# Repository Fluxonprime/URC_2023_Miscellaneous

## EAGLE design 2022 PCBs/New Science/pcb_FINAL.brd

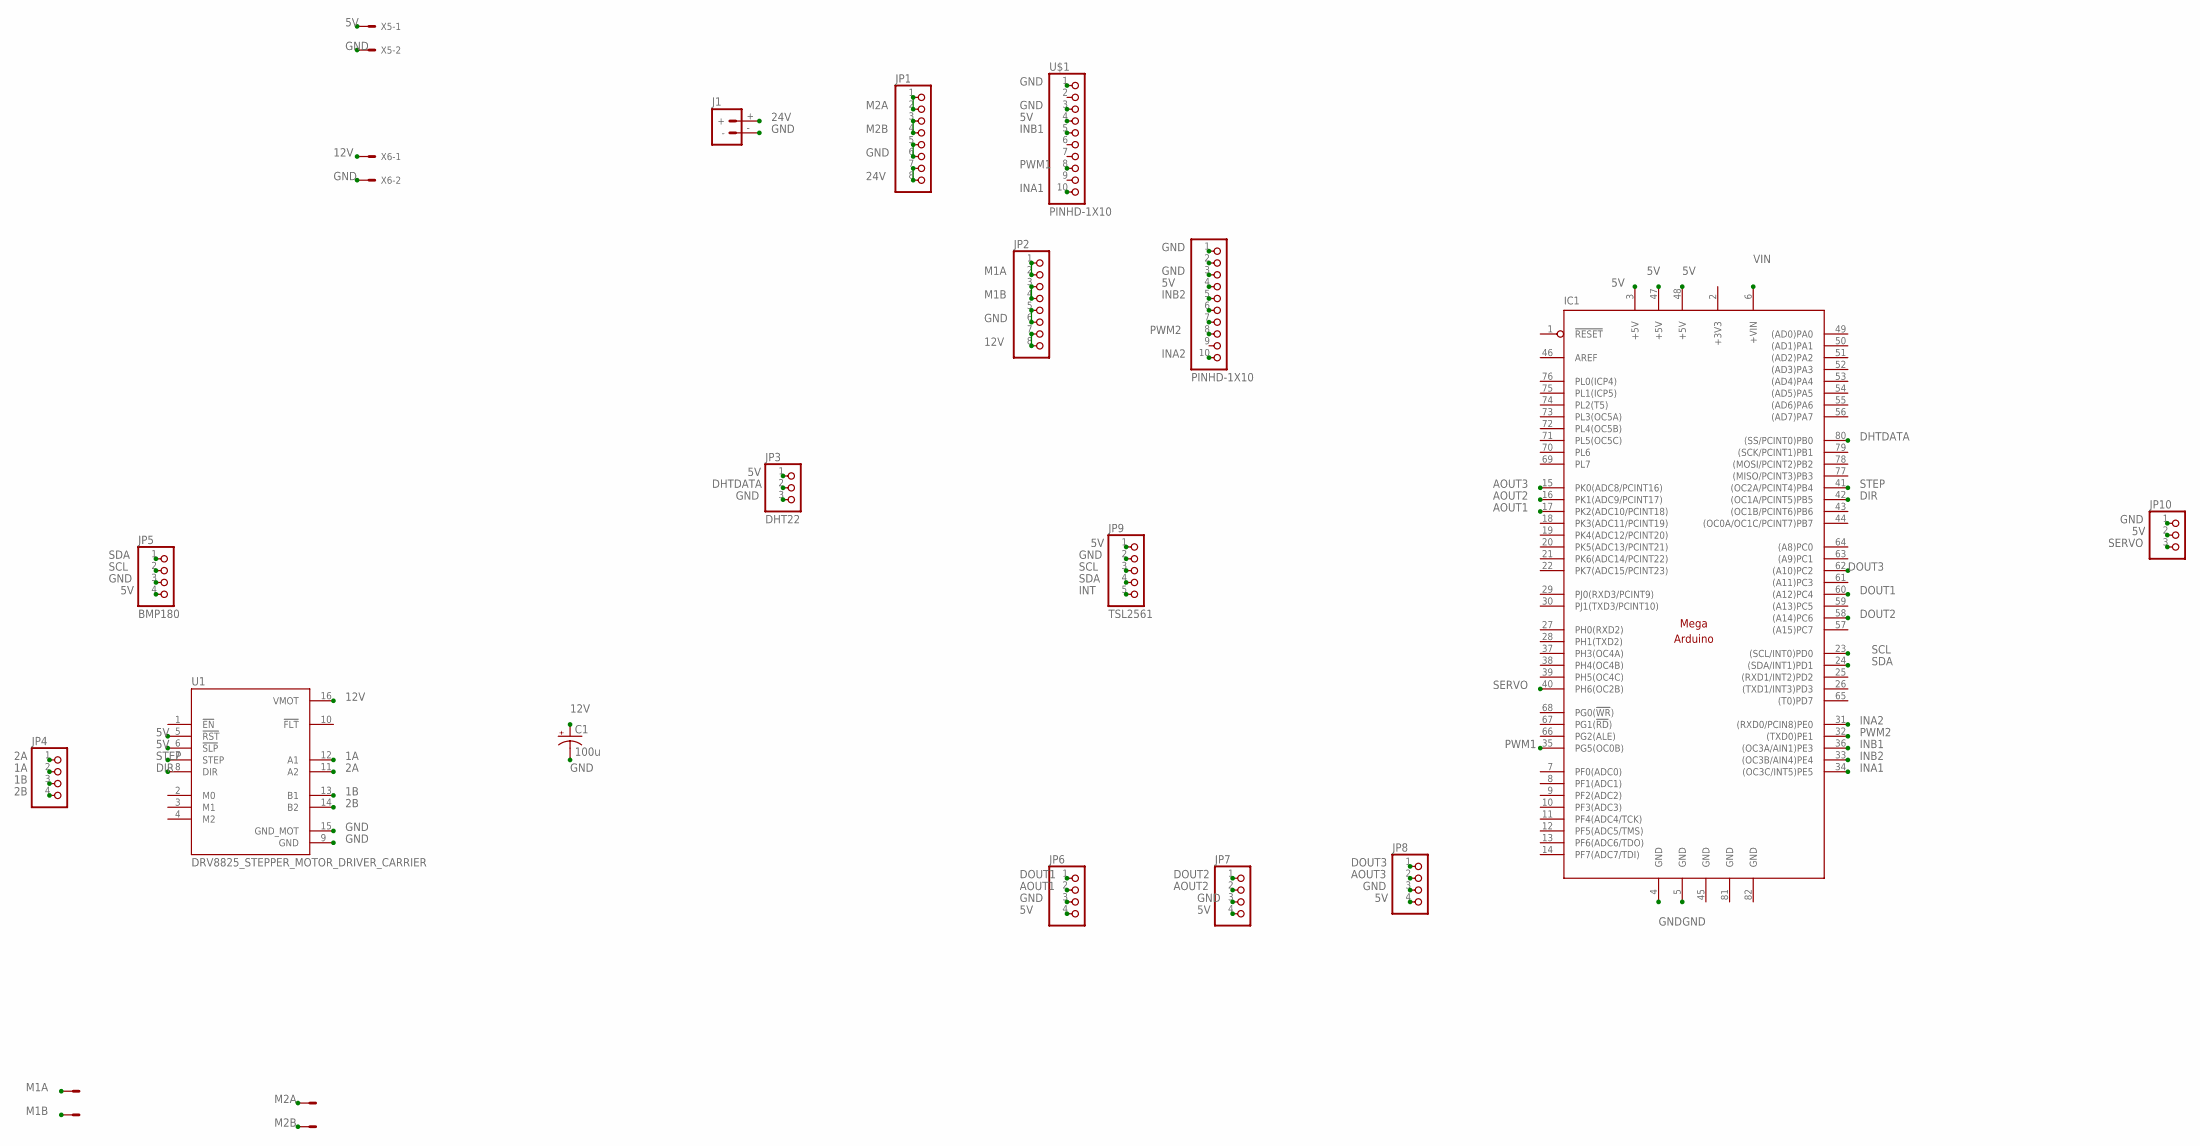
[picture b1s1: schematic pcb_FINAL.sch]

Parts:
C1: 100u; R/2012-12W
IC1: ARDUINO_MEGAARDUINO_11; ARDUINO_MEGA_ARDUINO_1
J1: BATTERY_CONN_DEANS; DEANS
JP1, JP2: PINHD-1X8BIG; 1X08-BIG
JP3: DHT22; 1X03
JP4, JP6, JP7, JP8: PINHD-1X4; 1X04
JP5: BMP180; 1X04
JP9: TSL2561; 1X05
JP10: PINHD-1X3; 1X03
U1: DRV8825_STEPPER_MOTOR_DRIVER_CARRIER; IC_DRV8825_STEPPER_MOTOR_DRIVER_CARRIER
U$1, U$2: PINHD-1X10; 1X10-BIG
X3, X4, X5, X6: KK-156-2

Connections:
1A: JP4.2, U1.12 (A1)
1B: JP4.3, U1.13 (B1)
2A: JP4.1, U1.11 (A2)
2B: JP4.4, U1.14 (B2)
5V: IC1.3 (+5V), IC1.47 (+5V), IC1.48 (+5V), JP3.1, JP5.4, JP6.4, JP7.4, JP8.4, JP9.1, JP10.2, U1.5 (!RST), U1.6 (!SLP), U$1.4, U$2.4, X5.1
12V: C1.+, JP2.7, JP2.8, U1.16 (VMOT), X6.1
24V: J1.+, JP1.7, JP1.8
+3V3: IC1.2 (+3V3)
AOUT1: IC1.17 (PK2(ADC10/PCINT18)), JP6.2
AOUT2: IC1.16 (PK1(ADC9/PCINT17)), JP7.2
AOUT3: IC1.15 (PK0(ADC8/PCINT16)), JP8.2
DHTDATA: IC1.80 ((SS/PCINT0)PB0), JP3.2
DIR: IC1.42 ((OC1A/PCINT5)PB5), U1.8 (DIR)
DOUT1: IC1.60 ((A12)PC4), JP6.1
DOUT2: IC1.58 ((A14)PC6), JP7.1
DOUT3: IC1.62 ((A10)PC2), JP8.1
GND: C1.-, IC1.4 (GND), IC1.5 (GND), IC1.45 (GND), IC1.81 (GND), IC1.82 (GND), J1.-, JP1.5, JP1.6, JP2.5, JP2.6, JP3.3, JP5.3, JP6.3, JP7.3, JP8.3, JP9.2, JP10.1, U1.9 (GND), U1.15 (GND_MOT), U$1.1, U$1.3, U$2.1, U$2.3, X5.2, X6.2
INA1: IC1.34 ((OC3C/INT5)PE5), U$1.10
INA2: IC1.31 ((RXD0/PCIN8)PE0), U$2.10
INB1: IC1.36 ((OC3A/AIN1)PE3), U$1.5
INB2: IC1.33 ((OC3B/AIN4)PE4), U$2.5
INT: JP9.5
M1A: JP2.1, JP2.2, X3.1
M1B: JP2.3, JP2.4, X3.2
M2A: JP1.1, JP1.2, X4.1
M2B: JP1.3, JP1.4, X4.2
PWM1: IC1.35 (PG5(OC0B)), U$1.8
PWM2: IC1.32 ((TXD0)PE1), U$2.8
SCL: IC1.23 ((SCL/INT0)PD0), JP5.2, JP9.3
SDA: IC1.24 ((SDA/INT1)PD1), JP5.1, JP9.4
SERVO: IC1.40 (PH6(OC2B)), JP10.3
STEP: IC1.41 ((OC2A/PCINT4)PB4), U1.7 (STEP)
VIN: IC1.6 (+VIN)

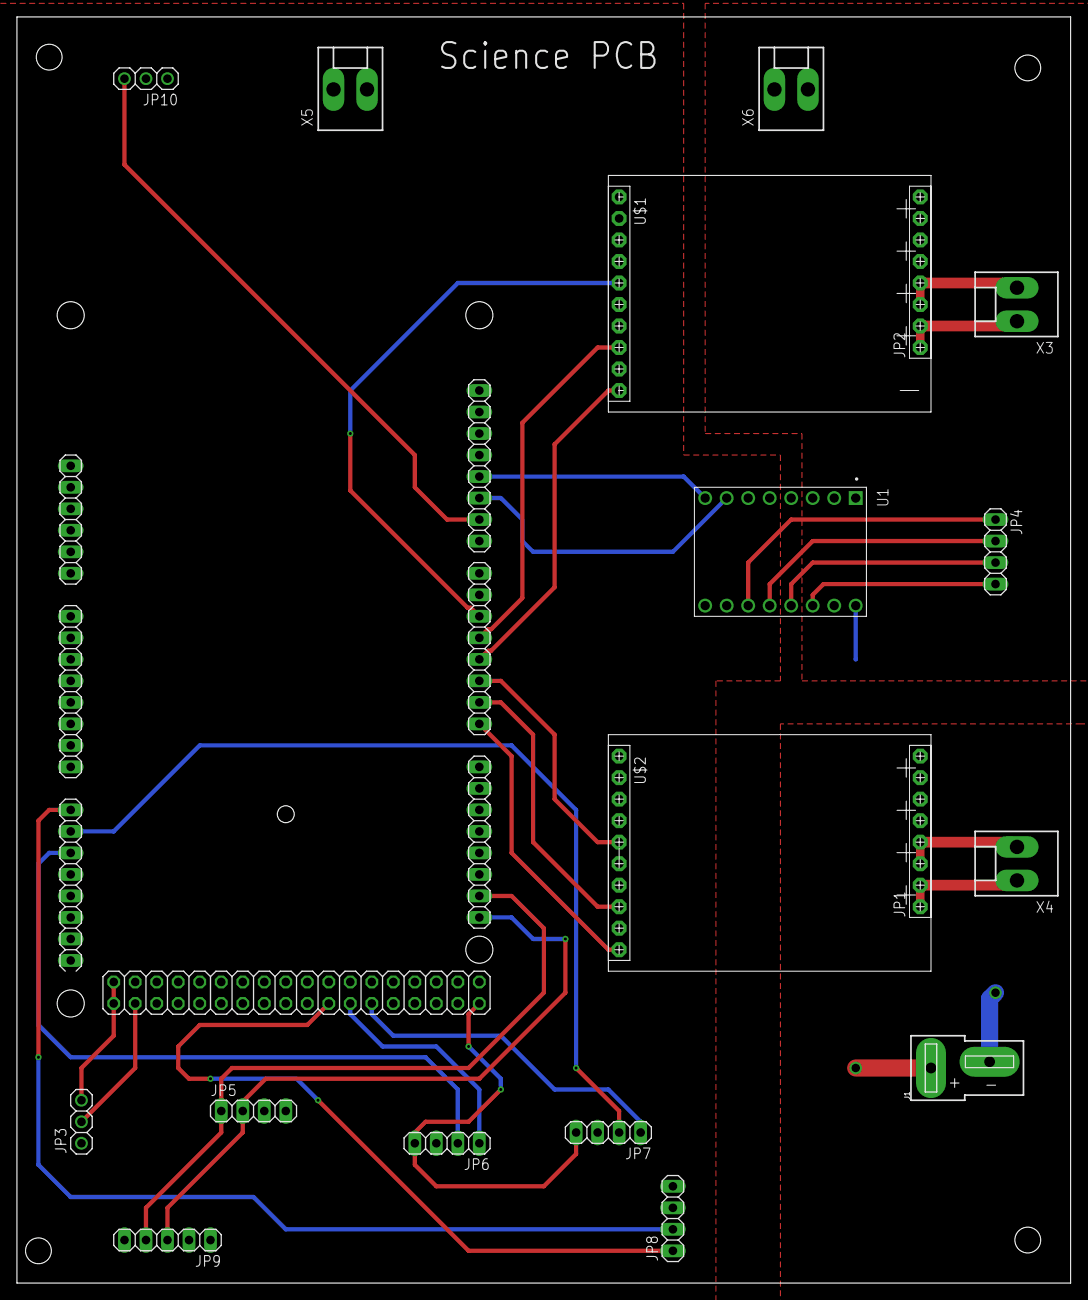
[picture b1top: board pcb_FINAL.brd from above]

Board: 2 copper layers, 124.4 x 149.5 mm, 20 parts (1 on the bottom side), 30 nets.

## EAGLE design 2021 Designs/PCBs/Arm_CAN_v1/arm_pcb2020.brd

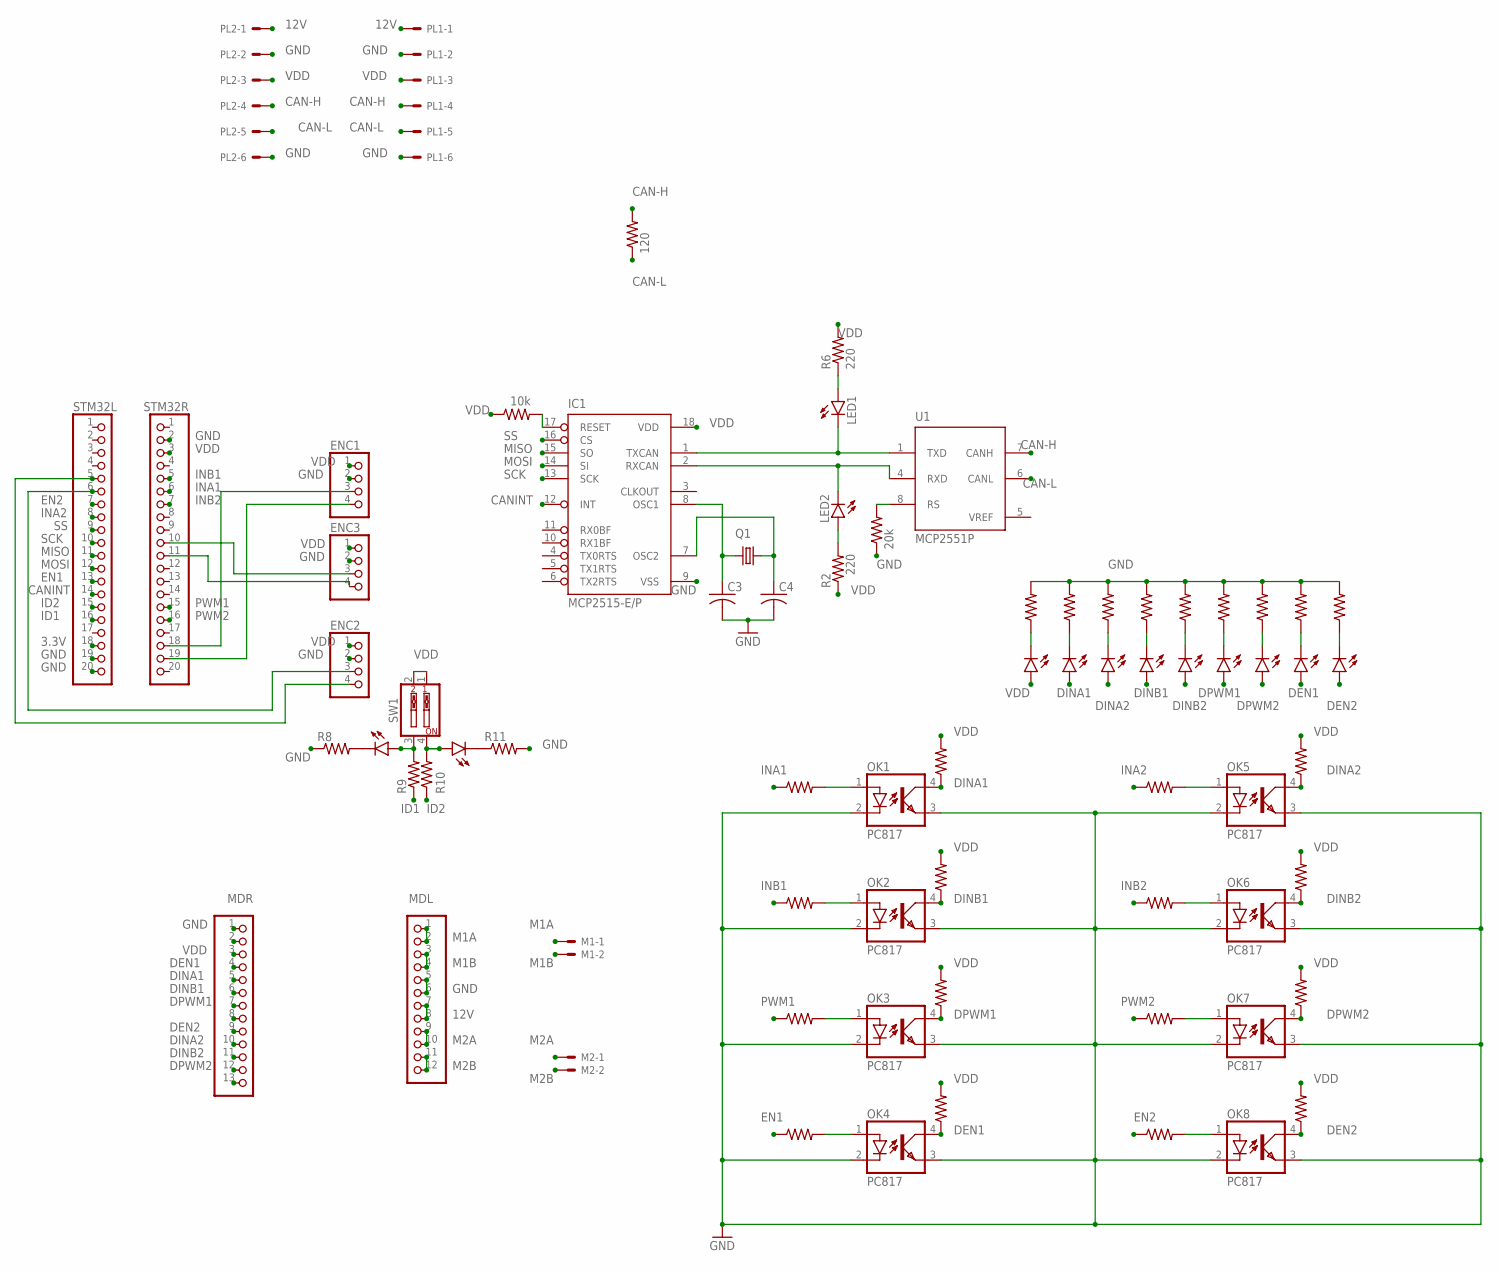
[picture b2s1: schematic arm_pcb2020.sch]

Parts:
C3, C4: C-US025-024X044; C025-024X044
ENC1, ENC2, ENC3: PINHD-1X4; 1X04
IC1: MCP2515-E/P; DIL18
JP2: MDL; 1X12
LED1, LED2, LED7, LED8, LED10, LED11, LED12, LED13, LED14, LED15, LED16, LED17, LED18: LEDSMT1206; 1206
M1, M2: 22-23-2021
MDR: MDR; 1X13
OK1, OK2, OK3, OK4, OK5, OK6, OK7, OK8: PC817; DIL04
PL1, PL2: 555X-6V; 5566-6
Q1: CRYSTALHC49U-V; HC49U-V
R2, R6: 220; R0805
R3: 120; 0207/9
R4, R5, R7, R8, R9, R10, R11, R12, R13, R14, R15, R16, R17, R18, R19, R20, R21, R22, R23, R24, R25, R26, R27, R28, R29, R33, R34, R37, R38: R-US_R0805; R0805
R39: 10k; 0207/10
R40: 20k; 0207/10
STM32L, STM32R: PINHD-1X20; 1X20
SW1: SW_DIP-2; EDG-02
U1: MCP2551P; DIL8

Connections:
3.3V: STM32L.18
12V: JP2.7, JP2.8, PL1.1, PL2.1
CAN-H: PL1.4, PL2.4, R3.2, U1.7 (CANH)
CAN-L: PL1.5, PL2.5, R3.1, U1.6 (CANL)
CANINT: IC1.12 (INT), STM32L.14
DEN1: LED17.A, MDR.4, OK4.4 (COL), R13.1
DEN2: LED18.A, MDR.9, OK8.4 (COL), R26.1
DINA1: LED11.A, MDR.5, OK1.4 (COL), R4.1
DINA2: LED12.A, MDR.10, OK5.4 (COL), R29.1
DINB1: LED13.A, MDR.6, OK2.4 (COL), R5.1
DINB2: LED14.A, MDR.11, OK6.4 (COL), R28.1
DPWM1: LED15.A, MDR.7, OK3.4 (COL), R12.1
DPWM2: LED16.A, MDR.12, OK7.4 (COL), R27.1
EN1: R23.1, STM32L.13
EN2: R38.1, STM32L.7
GND: C3.2, C4.2, ENC1.2, ENC2.2, ENC3.2, IC1.9 (VSS), JP2.5, JP2.6, MDR.1, OK1.2 (C), OK1.3 (EMIT), OK2.2 (C), OK2.3 (EMIT), OK3.2 (C), OK3.3 (EMIT), OK4.2 (C), OK4.3 (EMIT), OK5.2 (C), OK5.3 (EMIT), OK6.2 (C), OK6.3 (EMIT), OK7.2 (C), OK7.3 (EMIT), OK8.2 (C), OK8.3 (EMIT), PL1.2, PL1.6, PL2.2, PL2.6, R8.1, R11.2, R14.2, R15.2, R16.2, R17.2, R18.2, R19.2, R20.2, R33.2, R34.2, R40.1, STM32L.19, STM32L.20, STM32R.2
ID1: R9.1, STM32L.16
ID2: R10.1, STM32L.15
INA1: R7.1, STM32R.6
INA2: R24.1, STM32L.8
INB1: R21.1, STM32R.5
INB2: R25.1, STM32R.7
M1A: JP2.1, JP2.2, M1.1
M1B: JP2.3, JP2.4, M1.2
M2A: JP2.9, JP2.10, M2.1
M2B: JP2.11, JP2.12, M2.2
MISO: IC1.15 (SO), STM32L.11
MOSI: IC1.14 (SI), STM32L.12
unnamed: IC1.1 (TXCAN), LED1.C, U1.1 (TXD)
unnamed: R40.2, U1.8 (RS)
unnamed: C4.1, IC1.7 (OSC2), Q1.2
unnamed: C3.1, IC1.8 (OSC1), Q1.1
unnamed: LED11.C, R15.1
unnamed: ENC1.4, STM32R.19
unnamed: OK1.1 (A), R7.2
unnamed: LED12.C, R16.1
unnamed: IC1.17 (RESET), R39.2
unnamed: LED7.A, R9.2, SW1.3
unnamed: LED8.A, R10.2, SW1.4
unnamed: LED8.C, R11.1
unnamed: LED7.C, R8.2
unnamed: LED13.C, R17.1
unnamed: ENC2.4, STM32L.5
unnamed: OK2.1 (A), R21.2
unnamed: LED10.C, R14.1
unnamed: LED14.C, R18.1
unnamed: LED15.C, R19.1
unnamed: LED16.C, R20.1
unnamed: LED17.C, R33.1
unnamed: ENC2.3, STM32L.6
unnamed: ENC1.3, STM32R.18
unnamed: LED18.C, R34.1
unnamed: ENC3.3, STM32R.10
unnamed: LED2.A, R2.2
unnamed: ENC3.4, STM32R.11
unnamed: LED1.A, R6.1
unnamed: IC1.2 (RXCAN), LED2.C, U1.4 (RXD)
unnamed: OK3.1 (A), R22.2
unnamed: OK4.1 (A), R23.2
unnamed: OK5.1 (A), R24.2
unnamed: OK6.1 (A), R25.2
unnamed: OK7.1 (A), R37.2
unnamed: OK8.1 (A), R38.2
PWM1: R22.1, STM32R.15
PWM2: R37.1, STM32R.16
SCK: IC1.13 (SCK), STM32L.10
SS: IC1.16 (CS), STM32L.9
VDD: ENC1.1, ENC2.1, ENC3.1, IC1.18 (VDD), LED10.A, MDR.3, PL1.3, PL2.3, R2.1, R4.2, R5.2, R6.2, R12.2, R13.2, R26.2, R27.2, R28.2, R29.2, R39.1, STM32R.3, SW1.1, SW1.2, U1.3 (VDD)
VREF: U1.5 (VREF)
VSS: U1.2 (VSS)

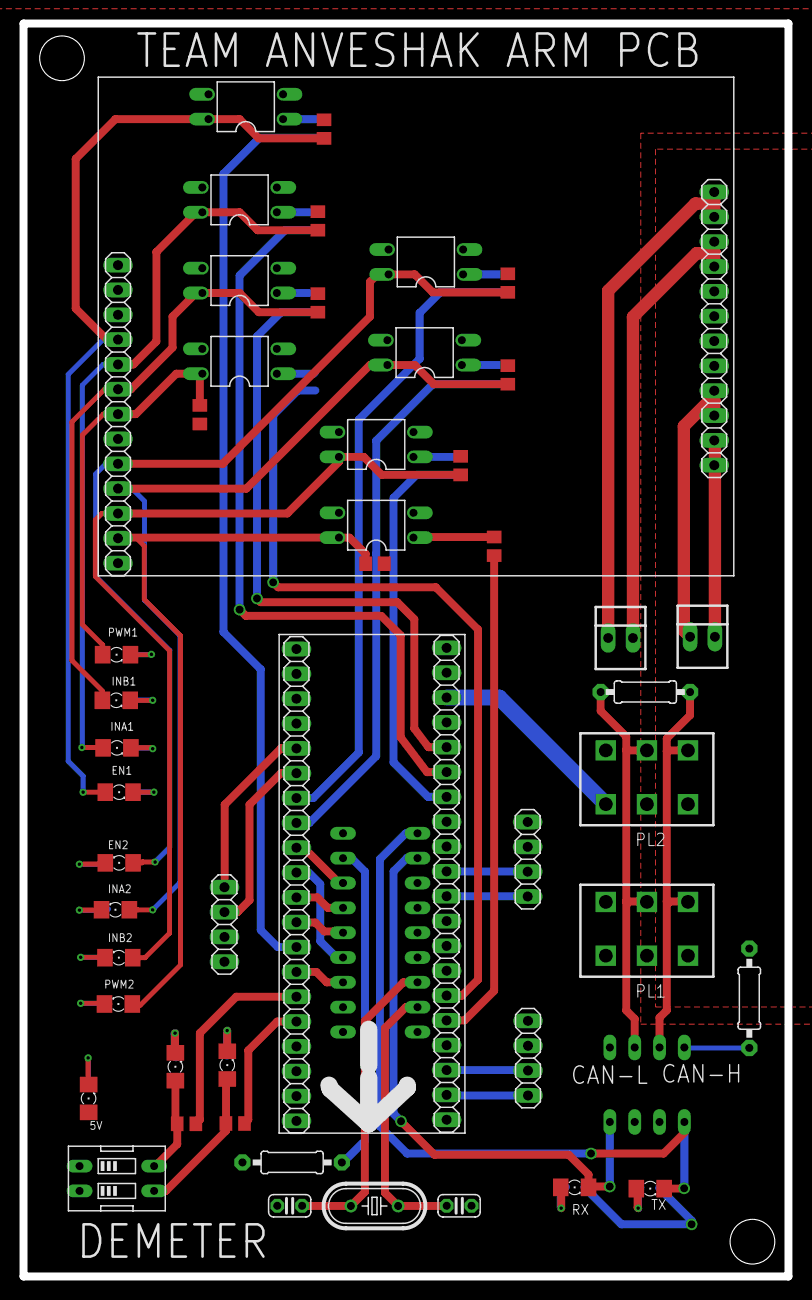
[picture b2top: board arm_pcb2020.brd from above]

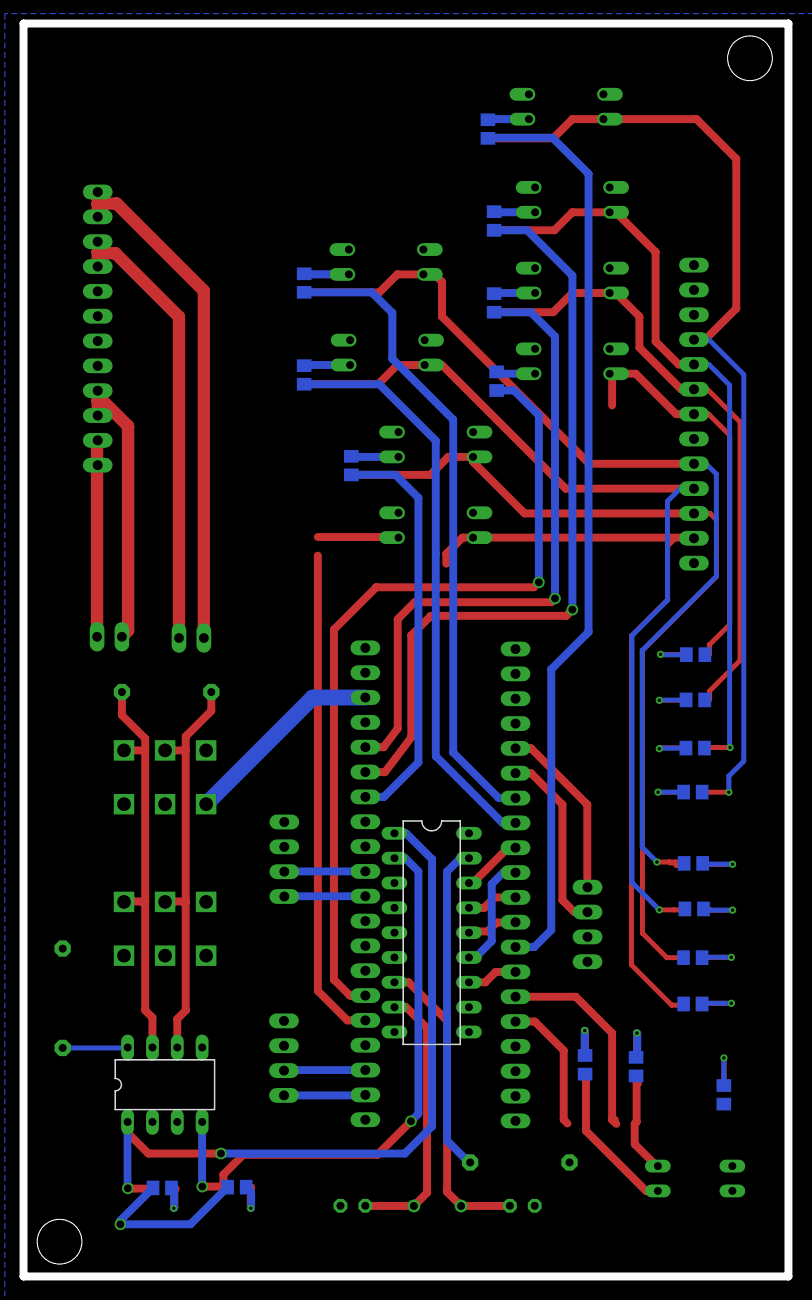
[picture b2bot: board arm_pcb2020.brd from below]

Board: 2 copper layers, 78.2 x 128.1 mm, 72 parts (22 on the bottom side), 67 nets.

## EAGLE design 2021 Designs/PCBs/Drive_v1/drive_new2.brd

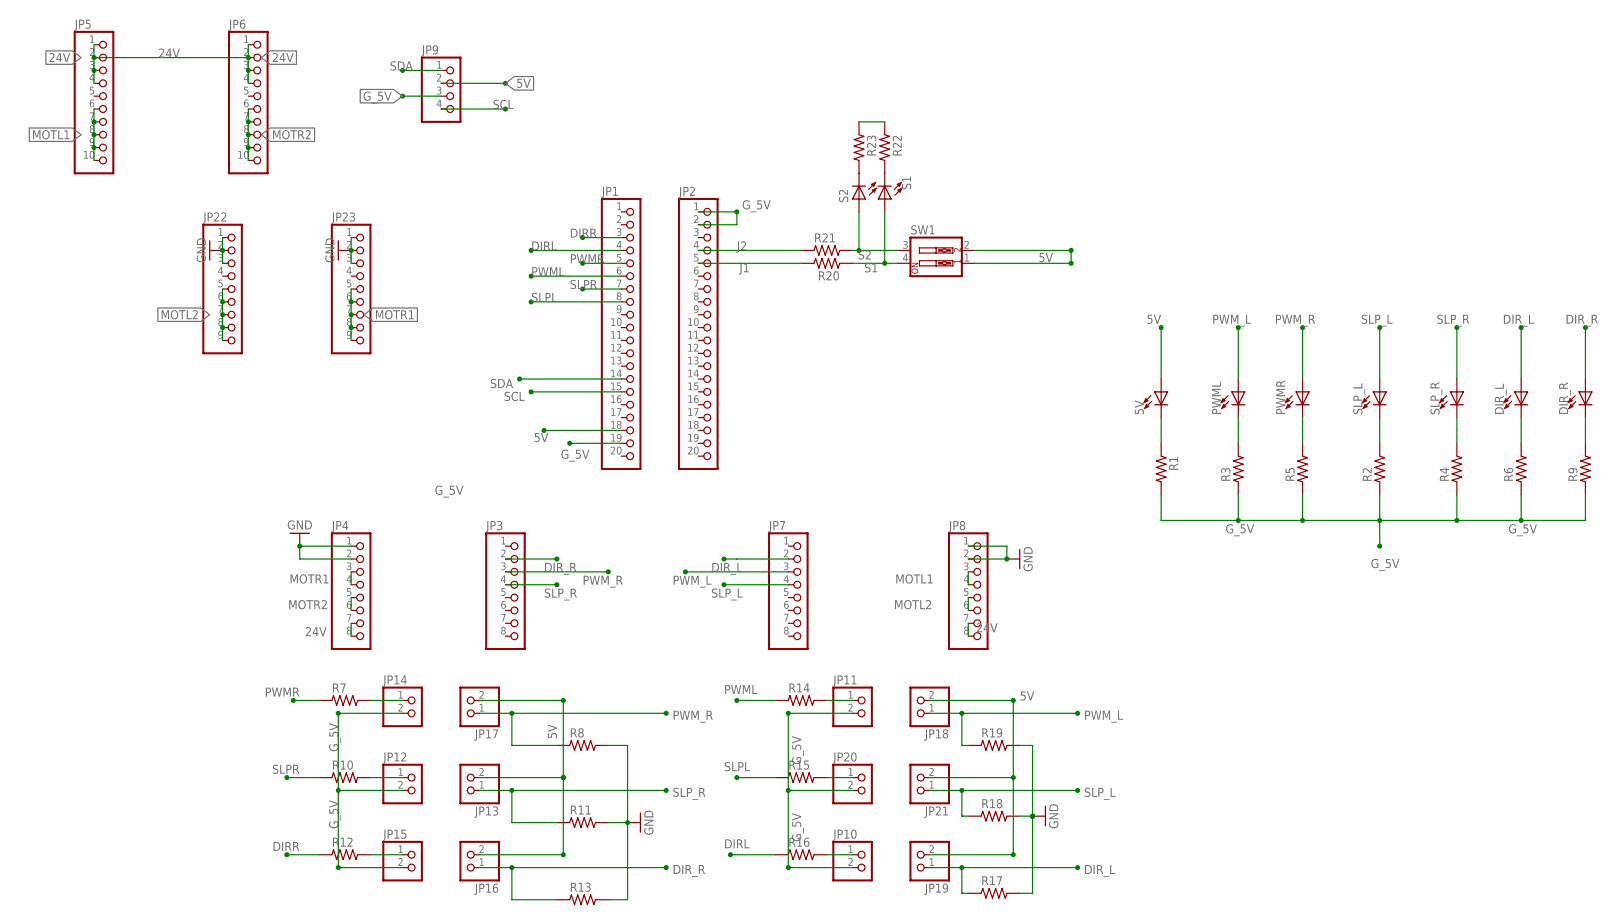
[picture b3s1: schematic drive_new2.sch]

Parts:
5V: RED; LED_1206
DIR_L: BLUE; LED_1206
DIR_R: BLUE; LED_1206
JP1, JP2: PINHD-1X20; 1X20
JP3, JP4, JP7, JP8: PINHD-1X8; 1X08
JP5, JP6: PINHD-1X10; 1X10
JP9: PINHD-1X4; 1X04
JP10, JP11, JP12, JP13, JP14, JP15, JP16, JP17, JP18, JP19, JP20, JP21: PINHD-1X2; 1X02
JP22, JP23: PINHD-1X9; 1X09
PWML: RED; LED_1206
PWMR: RED; LED_1206
R1, R2, R3, R4, R5, R6, R7, R8, R9, R10, R11, R12, R13, R14, R15, R16, R17, R18, R19, R20, R21, R22, R23: R_0805; R0805
S1, S2: RED; LED_1206
SLP_L: BLUE; LED_1206
SLP_R: BLUE; LED_1206
SW1: SW_DIP-2; EDG-02

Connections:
5V: 5V.A, JP1.18, JP9.2, JP13.2, JP16.2, JP17.2, JP18.2, JP19.2, JP21.2, SW1.1, SW1.2
24V: JP4.7, JP4.8, JP5.1, JP5.2, JP5.3, JP5.4, JP6.1, JP6.2, JP6.3, JP6.4, JP8.7, JP8.8
DIRL: JP1.4, R16.1
DIRR: JP1.3, R12.1
DIR_L: DIR_L.A, JP7.2, JP19.1, R17.1
DIR_R: DIR_R.A, JP3.2, JP16.1, R13.1
GND: JP4.1, JP4.2, JP8.1, JP8.2, JP22.1, JP22.2, JP22.3, JP23.1, JP23.2, JP23.3, R8.2, R11.2, R13.2, R17.2, R18.2, R19.2
G_5V: JP1.19, JP2.1, JP2.2, JP9.3, JP10.2, JP11.2, JP12.2, JP14.2, JP15.2, JP20.2, R1.2, R2.1, R3.1, R4.1, R5.1, R6.1, R9.1, R22.1, R23.1
J1: JP2.5, R20.2
J2: JP2.4, R21.2
MOTL1: JP5.6, JP5.7, JP5.8, JP5.9, JP5.10, JP8.3, JP8.4
MOTL2: JP8.5, JP8.6, JP22.5, JP22.6, JP22.7, JP22.8, JP22.9
MOTR1: JP4.3, JP4.4, JP23.5, JP23.6, JP23.7, JP23.8, JP23.9
MOTR2: JP4.5, JP4.6, JP6.6, JP6.7, JP6.8, JP6.9, JP6.10
unnamed: DIR_R.C, R9.2
unnamed: DIR_L.C, R6.2
unnamed: R4.2, SLP_R.C
unnamed: R2.2, SLP_L.C
unnamed: PWMR.C, R5.2
unnamed: PWML.C, R3.2
unnamed: 5V.C, R1.1
unnamed: JP14.1, R7.2
unnamed: JP12.1, R10.2
unnamed: R22.2, S1.C
unnamed: JP15.1, R12.2
unnamed: R23.2, S2.C
unnamed: JP11.1, R14.2
unnamed: JP20.1, R15.2
unnamed: JP10.1, R16.2
PWML: JP1.6, R14.1
PWMR: JP1.5, R7.1
PWM_L: JP7.3, JP18.1, PWML.A, R19.1
PWM_R: JP3.3, JP17.1, PWMR.A, R8.1
S1: R20.1, S1.A, SW1.4
S2: R21.1, S2.A, SW1.3
SCL: JP1.15, JP9.4
SDA: JP1.14, JP9.1
SLPL: JP1.8, R15.1
SLPR: JP1.7, R10.1
SLP_L: JP7.4, JP21.1, R18.1, SLP_L.A
SLP_R: JP3.4, JP13.1, R11.1, SLP_R.A

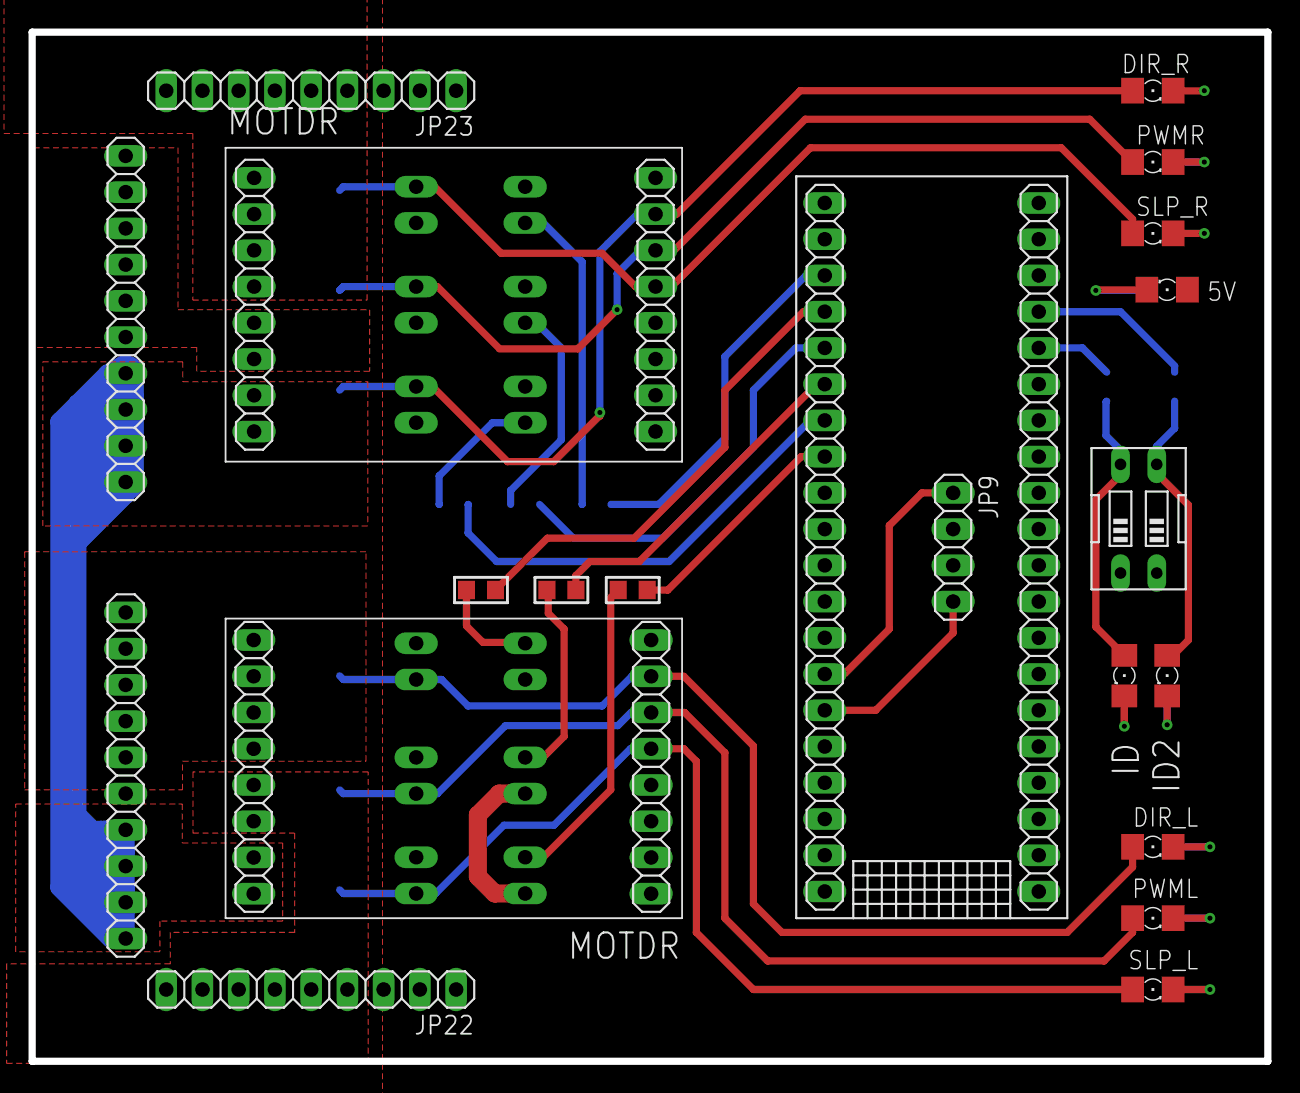
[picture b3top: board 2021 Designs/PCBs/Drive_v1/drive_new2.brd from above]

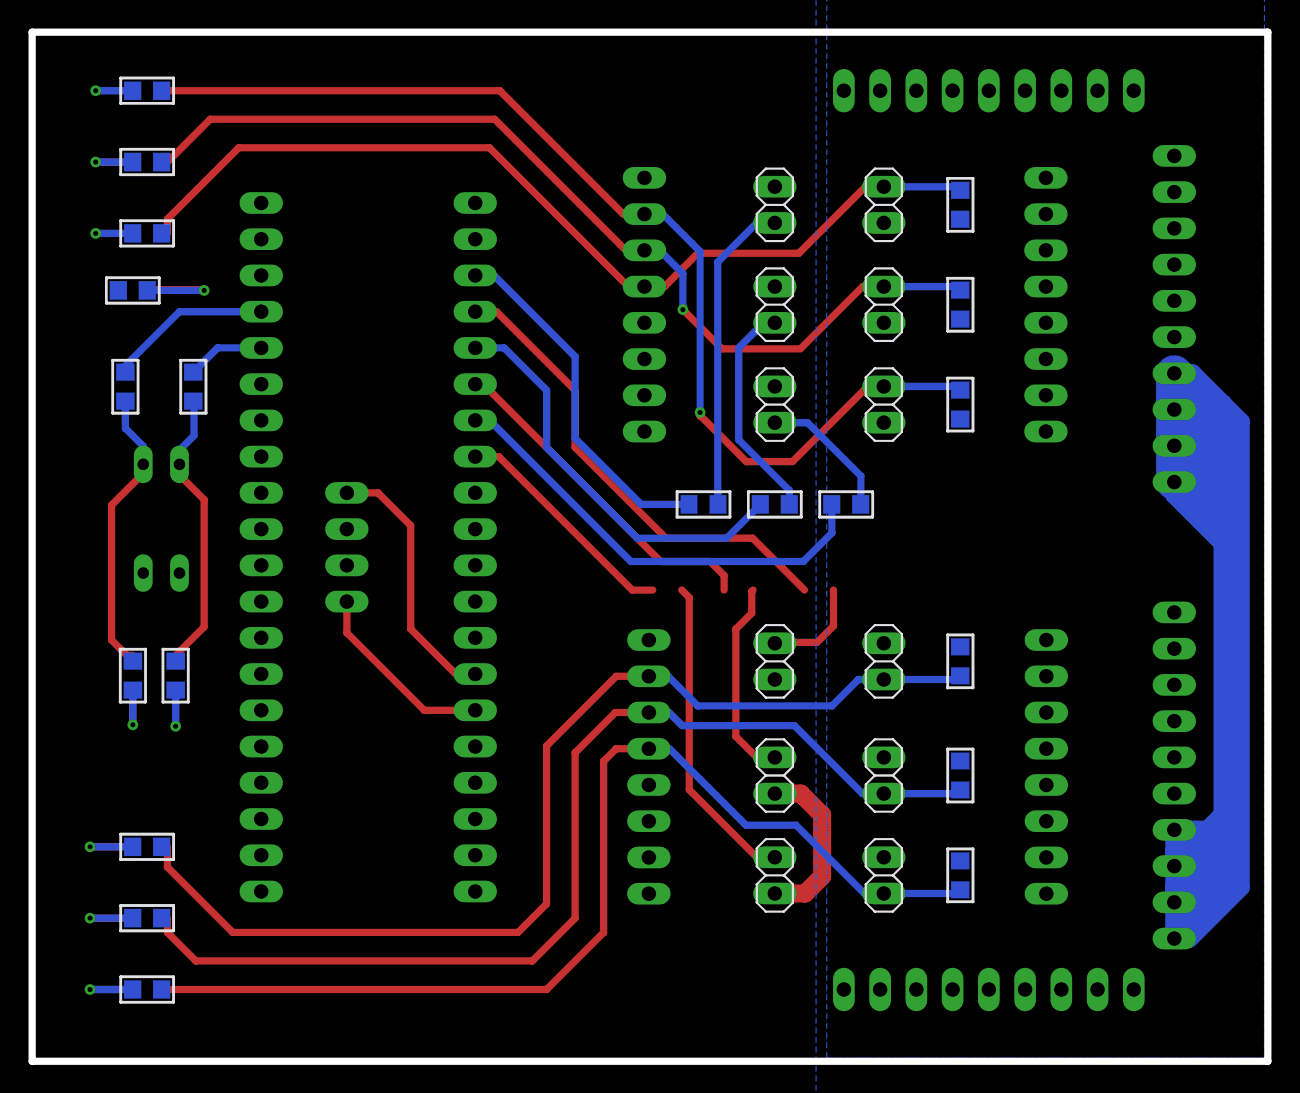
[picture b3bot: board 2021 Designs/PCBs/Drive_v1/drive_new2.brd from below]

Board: 2 copper layers, 86.6 x 72.1 mm, 56 parts (32 on the bottom side), 41 nets.

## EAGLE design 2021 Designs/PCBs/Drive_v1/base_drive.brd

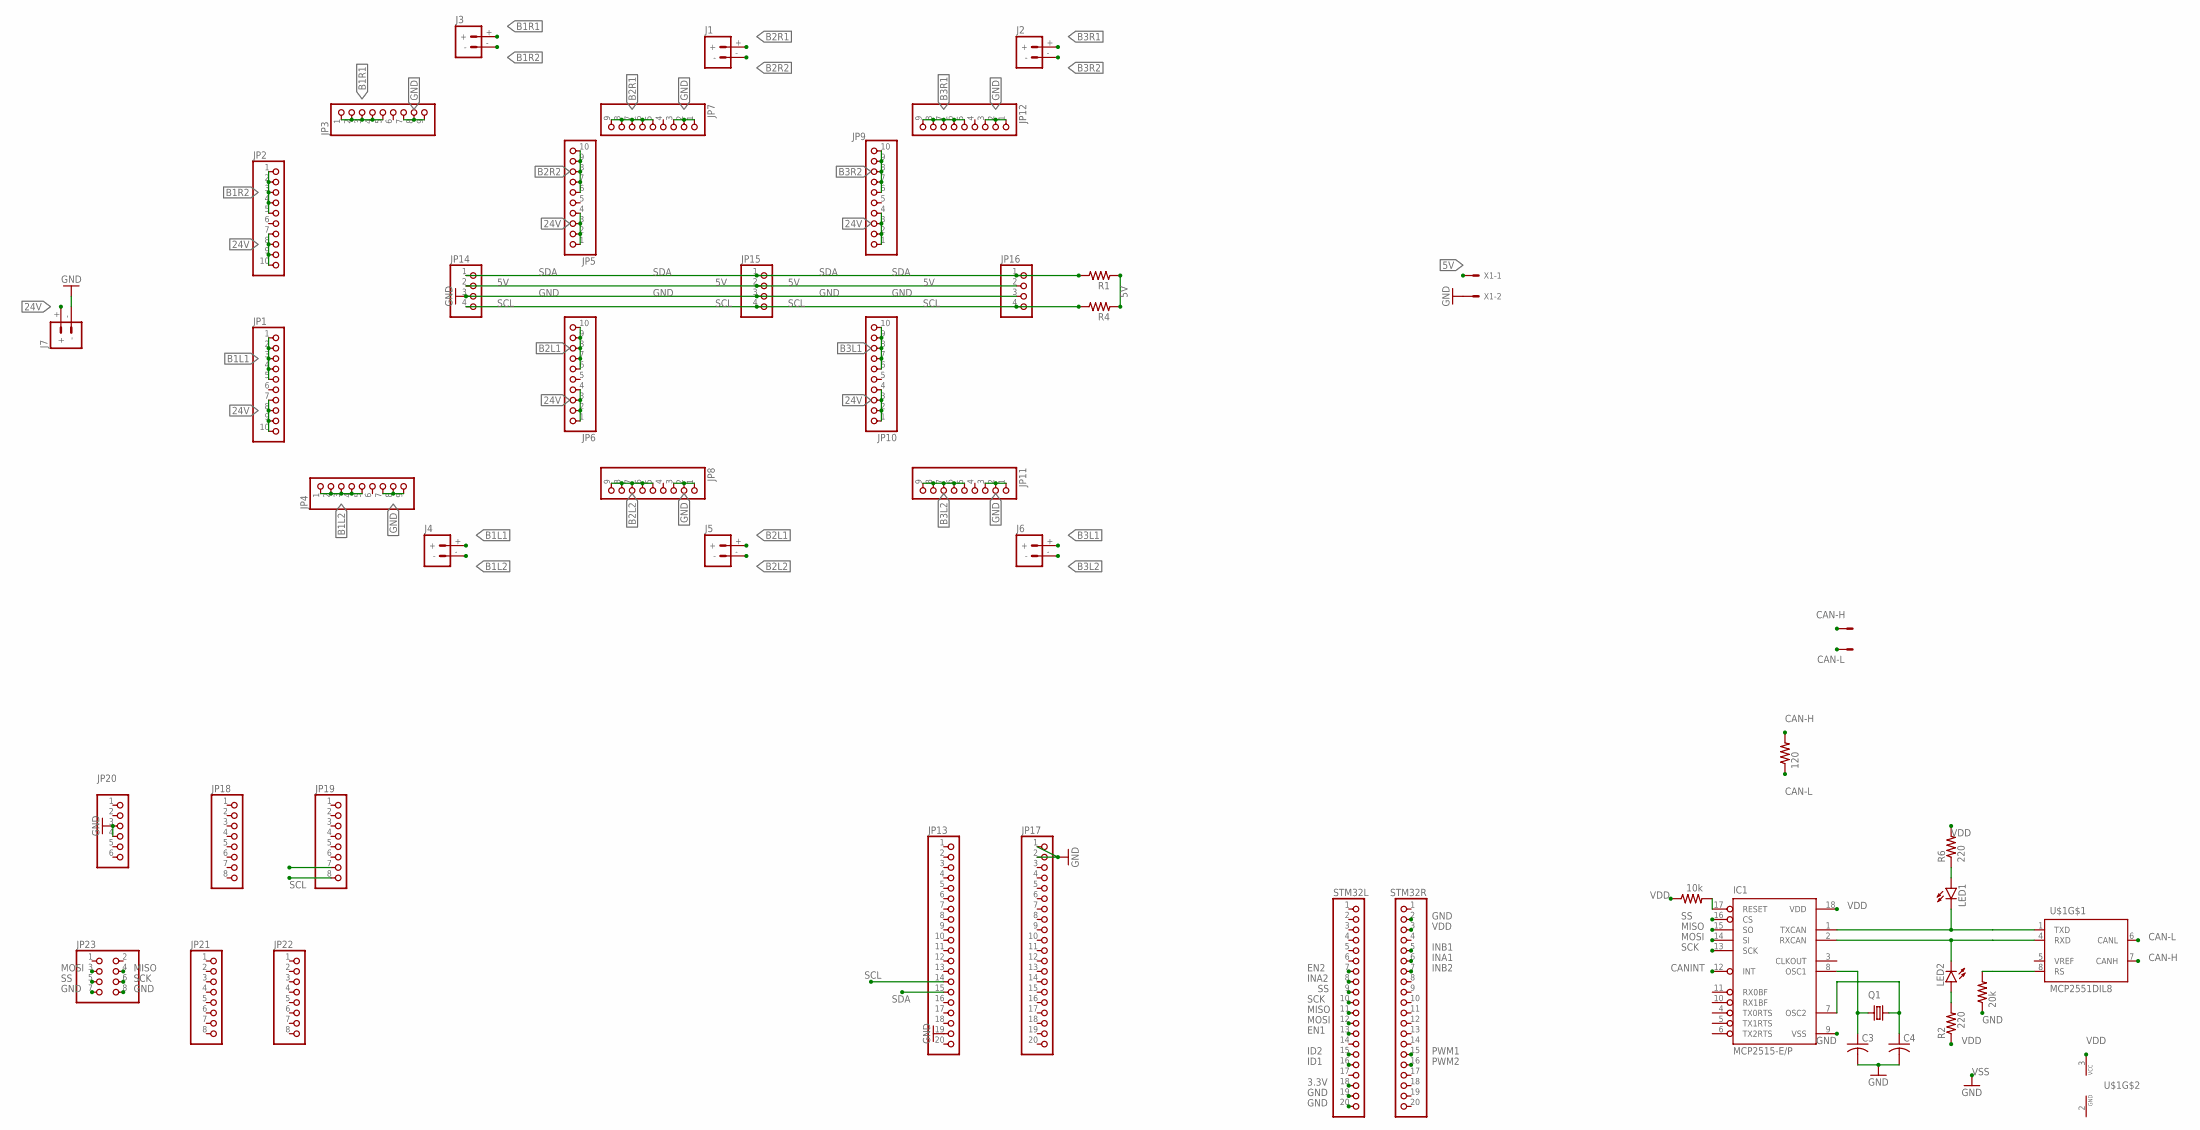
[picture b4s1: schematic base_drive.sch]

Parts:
C3, C4: C-US025-024X044; C025-024X044
IC1: MCP2515-E/P; DIL18
J1, J2, J3, J4, J5, J6, J7: BATTERY_CONN_DEANS; DEANS
JP1, JP2, JP5, JP6, JP9, JP10: PINHD-1X10; 1X10
JP3, JP4, JP7, JP8, JP11, JP12: PINHD-1X9; 1X09
JP13, JP17: PINHD-1X20; 1X20
JP14, JP15, JP16: PINHD-1X4; 1X04
JP18, JP19, JP21, JP22: PINHD-1X8; 1X08
JP20: PINHD-1X6; 1X06
JP23: PINHD-2X4; 2X04
LED1, LED2: LEDSMT1206; 1206
Q1: CRYSTALHC49U-V; HC49U-V
R1, R4: R_1206; R1206
R2, R6: 220; R0805
R3: 120; 0207/9
R39: 10k; 0207/10
R40: 20k; 0207/10
STM32L, STM32R: PINHD-1X20; 1X20
U$1: MCP2551DIL8; DIL08
X1, X2: KK-156-2

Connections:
3.3V: STM32L.18
5V: JP14.2, JP15.2, JP16.2, R1.1, R4.1, X1.1
24V: J7.+, JP1.7, JP1.8, JP1.9, JP1.10, JP2.7, JP2.8, JP2.9, JP2.10, JP5.1, JP5.2, JP5.3, JP5.4, JP6.1, JP6.2, JP6.3, JP6.4, JP9.1, JP9.2, JP9.3, JP9.4, JP10.1, JP10.2, JP10.3, JP10.4
B1L1: J4.+, JP1.1, JP1.2, JP1.3, JP1.4, JP1.5
B1L2: J4.-, JP4.1, JP4.2, JP4.3, JP4.4, JP4.5
B1R1: J3.+, JP3.1, JP3.2, JP3.3, JP3.4, JP3.5
B1R2: J3.-, JP2.1, JP2.2, JP2.3, JP2.4, JP2.5
B2L1: J5.+, JP6.6, JP6.7, JP6.8, JP6.9, JP6.10
B2L2: J5.-, JP8.5, JP8.6, JP8.7, JP8.8, JP8.9
B2R1: J1.+, JP7.5, JP7.6, JP7.7, JP7.8, JP7.9
B2R2: J1.-, JP5.6, JP5.7, JP5.8, JP5.9, JP5.10
B3L1: J6.+, JP10.6, JP10.7, JP10.8, JP10.9, JP10.10
B3L2: J6.-, JP11.5, JP11.6, JP11.7, JP11.8, JP11.9
B3R1: J2.+, JP12.5, JP12.6, JP12.7, JP12.8, JP12.9
B3R2: J2.-, JP9.6, JP9.7, JP9.8, JP9.9, JP9.10
CAN-H: R3.2, U$1.7 (CANH), X2.1
CAN-L: R3.1, U$1.6 (CANL), X2.2
CANINT: IC1.12 (INT)
EN1: STM32L.13
EN2: STM32L.7
GND: C3.2, C4.2, IC1.9 (VSS), J7.-, JP3.7, JP3.8, JP3.9, JP4.7, JP4.8, JP4.9, JP7.1, JP7.2, JP7.3, JP8.1, JP8.2, JP8.3, JP11.1, JP11.2, JP11.3, JP12.1, JP12.2, JP12.3, JP13.19, JP14.3, JP15.3, JP16.3, JP17.1, JP17.2, JP20.3, JP20.4, JP23.7, JP23.8, R40.1, STM32L.19, STM32L.20, STM32R.2, U$1.2 (GND), X1.2
ID1: STM32L.16
ID2: STM32L.15
INA1: STM32R.6
INA2: STM32L.8
INB1: STM32R.5
INB2: STM32R.7
MISO: IC1.15 (SO), JP23.4, STM32L.11
MOSI: IC1.14 (SI), JP23.3, STM32L.12
unnamed: IC1.1 (TXCAN), LED1.C, U$1.1 (TXD)
unnamed: R40.2, U$1.8 (RS)
unnamed: C4.1, IC1.7 (OSC2), Q1.2
unnamed: C3.1, IC1.8 (OSC1), Q1.1
unnamed: IC1.17 (RESET), R39.2
unnamed: LED2.A, R2.2
unnamed: LED1.A, R6.1
unnamed: IC1.2 (RXCAN), LED2.C, U$1.4 (RXD)
PWM1: STM32R.15
PWM2: STM32R.16
SCK: IC1.13 (SCK), JP23.6, STM32L.10
SCL: JP13.14, JP14.4, JP15.4, JP16.4, JP19.8, R4.2
SDA: JP13.15, JP14.1, JP15.1, JP16.1, JP19.7, R1.2
SS: IC1.16 (CS), JP23.5, STM32L.9
VDD: IC1.18 (VDD), R2.1, R6.2, R39.1, STM32R.3, U$1.3 (VCC)

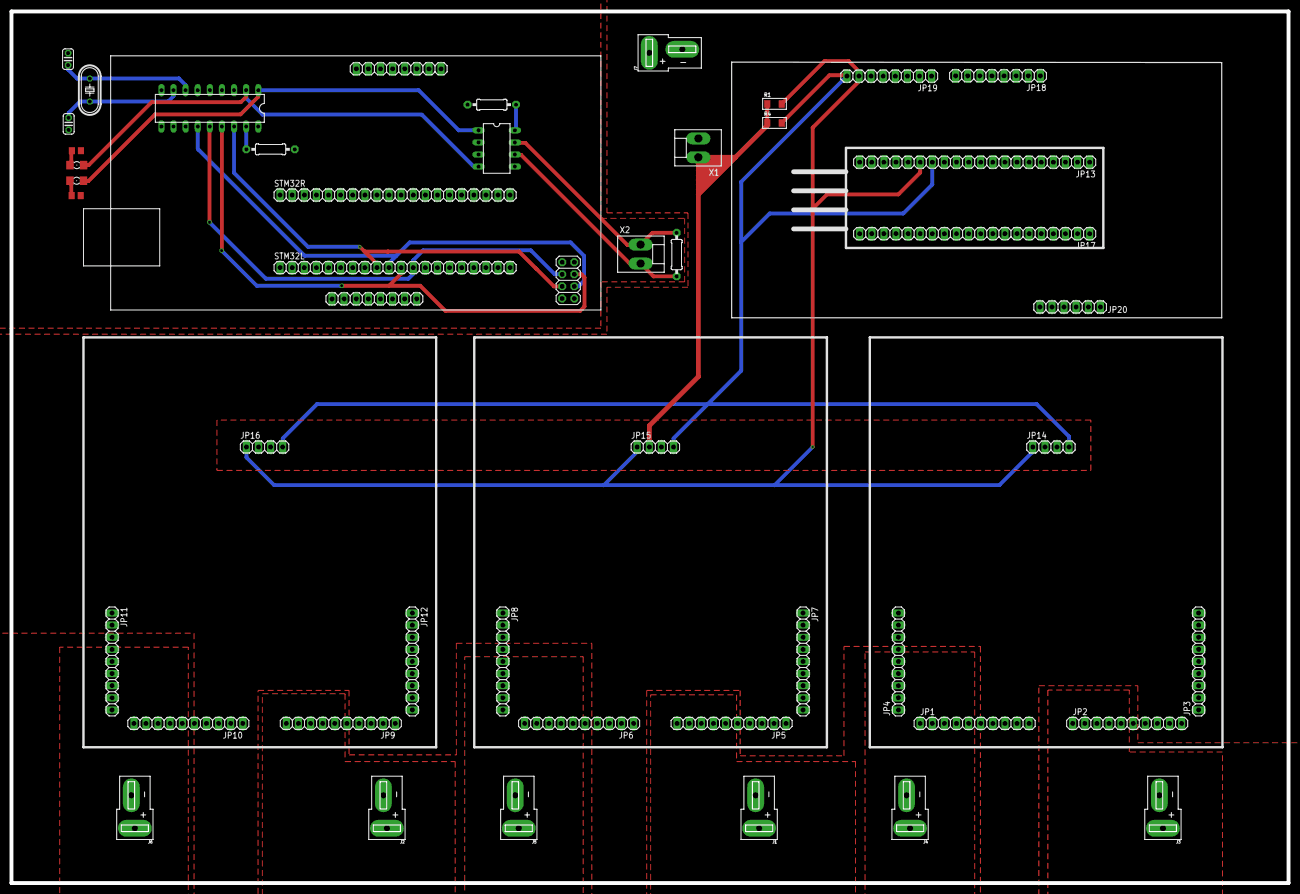
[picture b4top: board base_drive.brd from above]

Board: 2 copper layers, 268.0 x 182.9 mm, 48 parts (0 on the bottom side), 32 nets.

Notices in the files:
2022 PCBs/arm_base_2022/arm_base_2022/arm_slave_2022.brd:
©TeamAnveshak2022
parts and their libraries:
SparkFun-Connectors: Licensing: Creative Commons ShareAlike 4.0 International - https://creativecommons.org/licenses/by-sa/4.0
rc-master-smd: Copyright (C) 2007, Bob Starr
